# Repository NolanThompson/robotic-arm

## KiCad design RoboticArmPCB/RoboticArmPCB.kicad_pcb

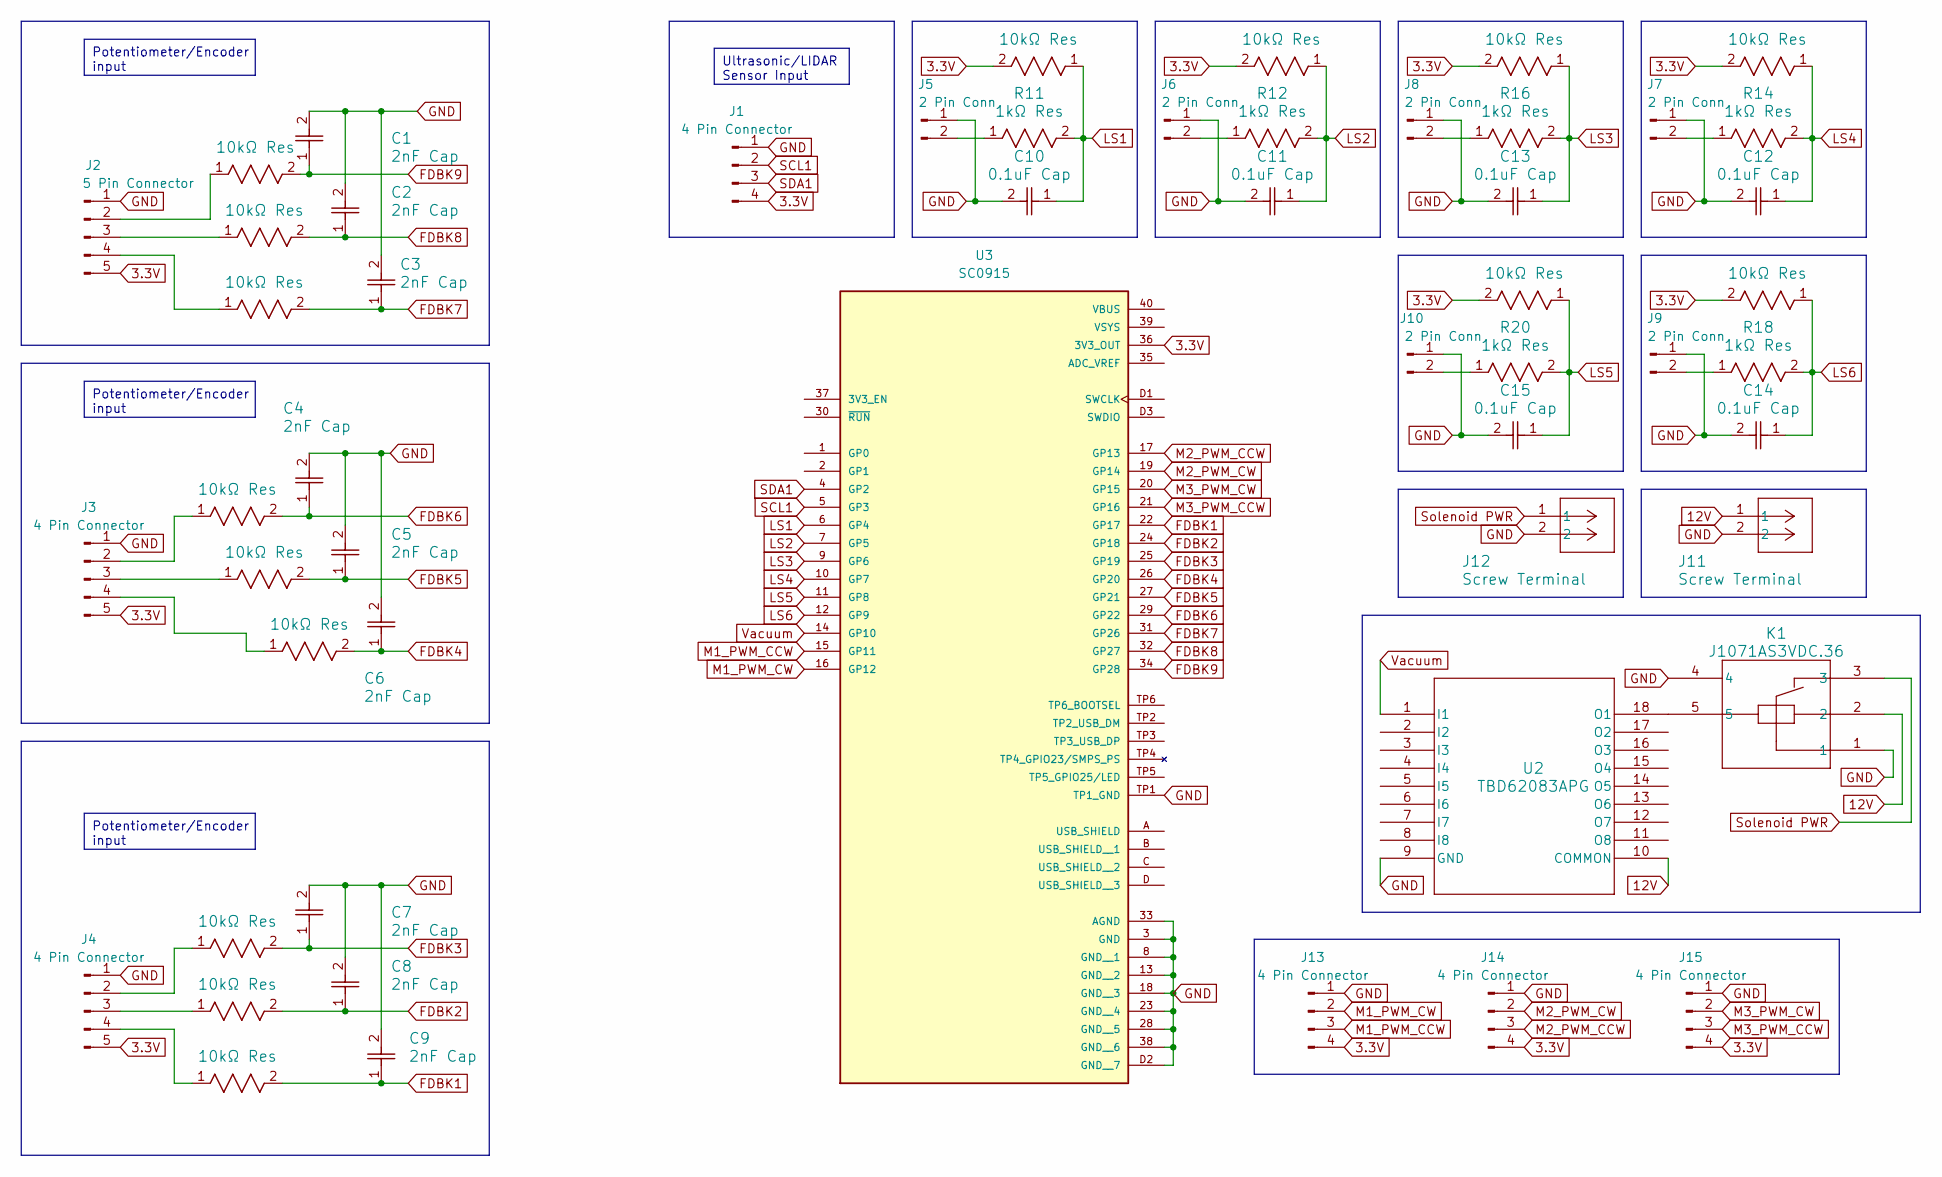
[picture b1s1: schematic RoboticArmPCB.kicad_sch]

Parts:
C1, C2, C3, C4, C5, C6, C7, C8, C9: 2nF Cap; CAP_CL21_SAM
C10, C11, C12, C13, C14, C15: 0.1uF Cap; CAP_CL10_SAM
J1, J13, J14, J15: 4 Pin Connector; PinHeader_1x04_P2.54mm_Vertical
J2: 5 Pin Connector; Molex_KK-254_AE-6410-05A_1x05_P2.54mm_Vertical
J3, J4: 4 Pin Connector; Molex_KK-254_AE-6410-05A_1x05_P2.54mm_Vertical
J5, J6, J7, J8, J9, J10: 2 Pin Conn; Molex_SL_171971-0002_1x02_P2.54mm_Vertical
J11, J12: Screw Terminal; CONN02_EBBA_10X7P6_ADM
K1: J1071AS3VDC.36; RELAY5_J1071A_CRS
R1, R2, R3, R4, R5, R6, R7, R8, R9, R10, R13, R15, R17, R19, R21: 10kΩ Res; RES_WR06_WRE
R11, R12, R14, R16, R18, R20: 1kΩ Res; RES_WR08_WRE
U2: TBD62083APG; P-DIP18-300-2p54-001_TOS
U3: SC0915; MODULE_SC0915; PARTREV 1.9

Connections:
3.3V: J1.4, J2.5, J3.5, J4.5, J13.4, J14.4, J15.4, R10.2, R13.2, R15.2, R17.2, R19.2, R21.2, U3.36 (3V3_OUT)
12V: J11.1, K1.2, U2.10 (COMMON)
FDBK1: C9.1, R9.2, U3.22 (GP17)
FDBK2: C8.1, R8.2, U3.24 (GP18)
FDBK3: C7.1, R7.2, U3.25 (GP19)
FDBK4: C6.1, R6.2, U3.26 (GP20)
FDBK5: C5.1, R5.2, U3.27 (GP21)
FDBK6: C4.1, R4.2, U3.29 (GP22)
FDBK7: C3.1, R3.2, U3.31 (GP26)
FDBK8: C2.1, R2.2, U3.32 (GP27)
FDBK9: C1.1, R1.2, U3.34 (GP28)
GND: C1.2, C2.2, C3.2, C4.2, C5.2, C6.2, C7.2, C8.2, C9.2, C10.2, C11.2, C12.2, C13.2, C14.2, C15.2, J1.1, J2.1, J3.1, J4.1, J5.1, J6.1, J7.1, J8.1, J9.1, J10.1, J11.2, J12.2, J13.1, J14.1, J15.1, K1.1, K1.4, U2.9 (GND), U3.3 (GND), U3.8 (GND__1), U3.13 (GND__2), U3.18 (GND__3), U3.23 (GND__4), U3.28 (GND__5), U3.33 (AGND), U3.38 (GND__6), U3.D2 (GND__7), U3.TP1 (TP1_GND)
LS1: C10.1, R10.1, R11.2, U3.6 (GP4)
LS2: C11.1, R12.2, R13.1, U3.7 (GP5)
LS3: C13.1, R16.2, R17.1, U3.9 (GP6)
LS4: C12.1, R14.2, R15.1, U3.10 (GP7)
LS5: C15.1, R20.2, R21.1, U3.11 (GP8)
LS6: C14.1, R18.2, R19.1, U3.12 (GP9)
M1_PWM_CCW: J13.3, U3.15 (GP11)
M1_PWM_CW: J13.2, U3.16 (GP12)
M2_PWM_CCW: J14.3, U3.17 (GP13)
M2_PWM_CW: J14.2, U3.19 (GP14)
M3_PWM_CCW: J15.3, U3.21 (GP16)
M3_PWM_CW: J15.2, U3.20 (GP15)
unnamed: J2.2, R1.1
unnamed: J2.3, R2.1
unnamed: J2.4, R3.1
unnamed: J3.2, R4.1
unnamed: J3.3, R5.1
unnamed: J3.4, R6.1
unnamed: J4.2, R7.1
unnamed: J4.3, R8.1
unnamed: J4.4, R9.1
unnamed: J5.2, R11.1
unnamed: J6.2, R12.1
unnamed: J7.2, R14.1
unnamed: J8.2, R16.1
unnamed: J9.2, R18.1
unnamed: J10.2, R20.1
unnamed: K1.5, U2.18 (O1)
SCL1: J1.2, U3.5 (GP3)
SDA1: J1.3, U3.4 (GP2)
Solenoid PWR: J12.1, K1.3
Vacuum: U2.1 (I1), U3.14 (GP10)

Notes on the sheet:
Potentiometer/Encoder input
Ultrasonic/LIDAR Sensor Input

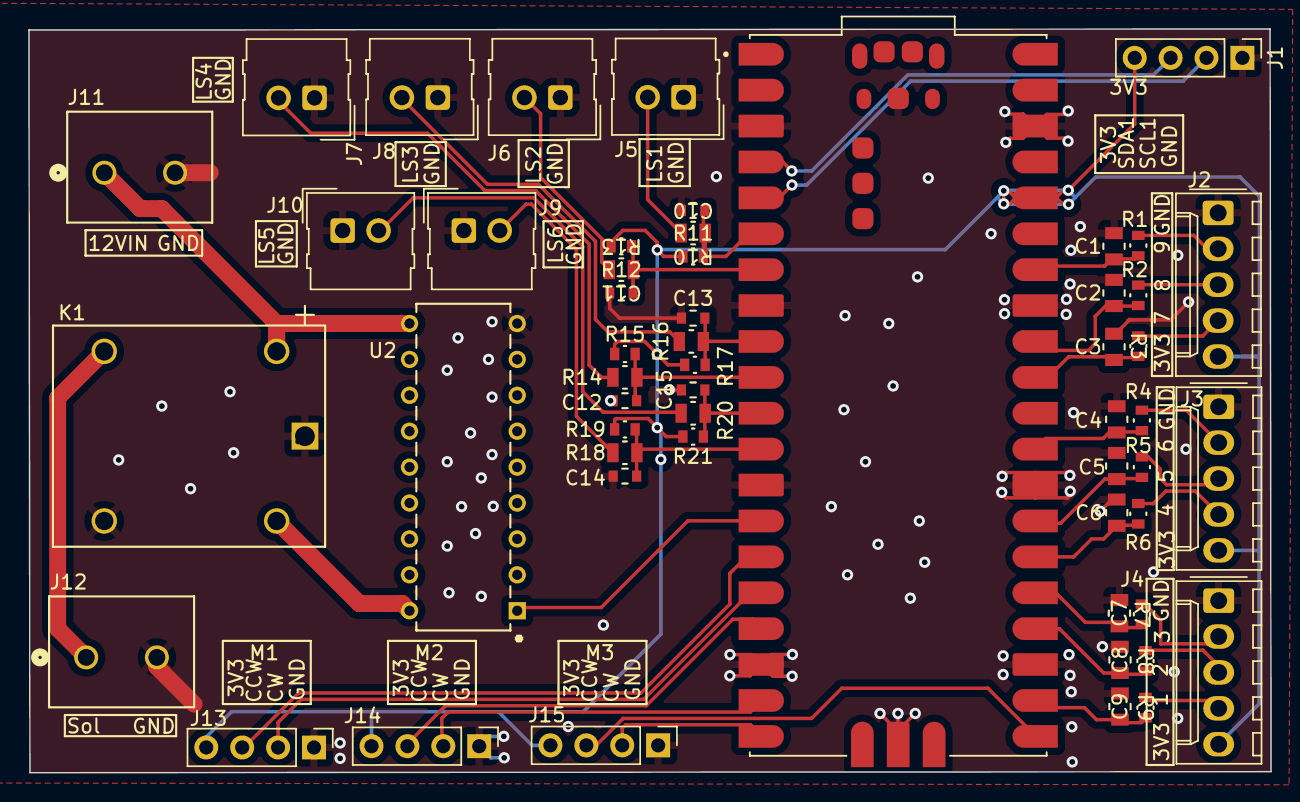
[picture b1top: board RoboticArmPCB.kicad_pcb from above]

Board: 2 copper layers, 87.9 x 52.6 mm, 54 parts (0 on the bottom side), 44 nets.

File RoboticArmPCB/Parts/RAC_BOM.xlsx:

https://www.digikey.com/short/0hcv8r0n
Item | Qty | Link | Reference(s) | Value | LibPart | Footprint | Datasheet
1 | 100 | CL21B202KBANNNC | C1, C2, C3, C4, C5, C6, C7, C8, C9 | 2nF Cap | CL21B202KBANNNC:CL21B202KBANNNC | CAP_CL21_SAM | CL21B202KBANNNC
2 | 200 | CL10B104KB8NNWC | C10, C11, C12, C13, C14, C15 | 0.1uF Cap | CL10B104KB8NNWC:CL10B104KB8NNWC | CAP_CL10_SAM | CL10B104KB8NNWC
7 | 10 | EBBA-02-C-SS-BU | J11, J12 | Screw Terminal | EBBA_02_C_SS_BU:EBBA-02-C-SS-BU | CONN02_EBBA_10X7P6_ADM | EBBA-02-C-SS-BU
8 | 10 | J1071AS3VDC.36 | K1 | J1071AS3VDC.36 | J1071AS3VDC_36:J1071AS3VDC.36 | RELAY5_J1071A_CRS | J1071AS3VDC.36
9 | 500 | CR0603-FX-1002ELFCT-ND | R1, R2, R3, R4, R5, R6, R7, R8, R9, R10, R13, R15, R17, R19, R21 | 10kΩ Res | WR06X1002FTL:WR06X1002FTL | RES_WR06_WRE | WR06X1002FTL |  | Replaced: Was WR06X1002FTL
10 | 500 | WR08X102 JTL | R11, R12, R14, R16, R18, R20 | 1kΩ Res | WR08X102_JTL:WR08X102_JTL | RES_WR08_WRE | WR08X102 JTL
11 | 4 | SC0915 | U1 | SC0915 | SC0915:SC0915 | SC0918:MODULE_SC0918
12 | 5 | TBD62083APG | U2 | TBD62083APG | TBD62083APG:TBD62083APG | P-DIP18-300-2p54-001_TOS | TBD62083APG

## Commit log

2024-04-15 trying to build
2024-04-15 resolving runtime warnings
2024-04-23 adding gitignore
2024-04-23 Final
2024-04-23 removed unnecesary code
2024-04-23 updated final revision
2024-04-23 removed pointless files
